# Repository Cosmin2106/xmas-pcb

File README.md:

# ATtiny-powered Christmas Tree

The goal of this project was to create a Christmas decoration that houses a secret puzzle.
The implementation is based around the Microchip ATtiny25V at 1 MHz, which offers 5 GPIO pins with pin change interrupts.
The board is driven by a single CR2032 battery and features a button for user input.

The MCU can be either programmed using the exposed connectors of the "tree trunk", or with an SOIC-8 clip.
In my case, I opted for the latter.
Details regarding the programmer can be found in [this repository](https://github.com/Cosmin2106/arduinoisp-attiny-8-pin-pcb).

## Modes of Operation

When we turn on the board, we can perform a quick check to see if the button is already being held down or not.
If we encounter a normal power cycle, we enter **christmas decoration mode**.
The button is now dedicated to cycling through different prebuilt light shows.
If the button is being pressed at boot, we enter **game mode** instead.
The game idea is inspired by [Pop The Lock](https://apps.apple.com/us/app/pop-the-lock/id979100082) and [Stop Me](https://github.com/SolderedElectronics/-Stop-me-game-solder-kit).
To optimize flash usage, we *emulate randomness* by using a linear congruential generator as PRNG.
At the end of each game, the board displays the total number of points using the "branch" LEDs: one left blink means +10, one right blink, +1.
Using EEPROM flags, we can remember if the user surpassed a hard-coded points threshold in order to unlock secret light shows in the other mode.

## BOM

Designator | Footprint | Quantity | Details
---------- | --------- | -------- | -------
BT1 | Renata_HU2032LF | 1 | Renata 701106 holder for CR2032
C1 | 402 | 1 | Ceramic 100 nF
C2 | 402 | 1 | Ceramic 10 uF
D1, D11, D3, D5, D7, D9 | 603 | 6 | Osram LO L29K-J2L1-24-0-2-R18-Z
D10, D12, D2, D4, D6, D8 | 603 | 6 | Osram LY L29K-H1K2-26-0-2-R18-Z
R1, R2, R3, R4 | 402 | 4 | 150 Ω
SW1 | SW_Push_1P1T_NO_CK_KMR2 | 1 | C&K KMR421NGLFS
SW3 | SW_DPDT_CK_JS202011JCQN | 1 | C&K JS202011JCQN
U1 | SOIC-8_5.3x5.3mm_P1.27mm | 1 | ATtiny25V-10SU

## Photos

#### Image Licenses:

- <a href="https://www.flaticon.com/free-icons/ball" title="ball icons">Ball icons created by Good Ware - Flaticon</a>
- <a href="https://www.flaticon.com/free-icons/snowflake" title="snowflake icons">Snowflake icons created by Good Ware - Flaticon</a>
- <a href="https://www.flaticon.com/free-icons/snowflake" title="snowflake icons">Snowflake icons created by kmg design - Flaticon</a>

#### Improvements?

If you have ideas for improvements, please don't hesitate to reach out!
Since this is my first custom PCB project, advice would be highly appreciated! :D

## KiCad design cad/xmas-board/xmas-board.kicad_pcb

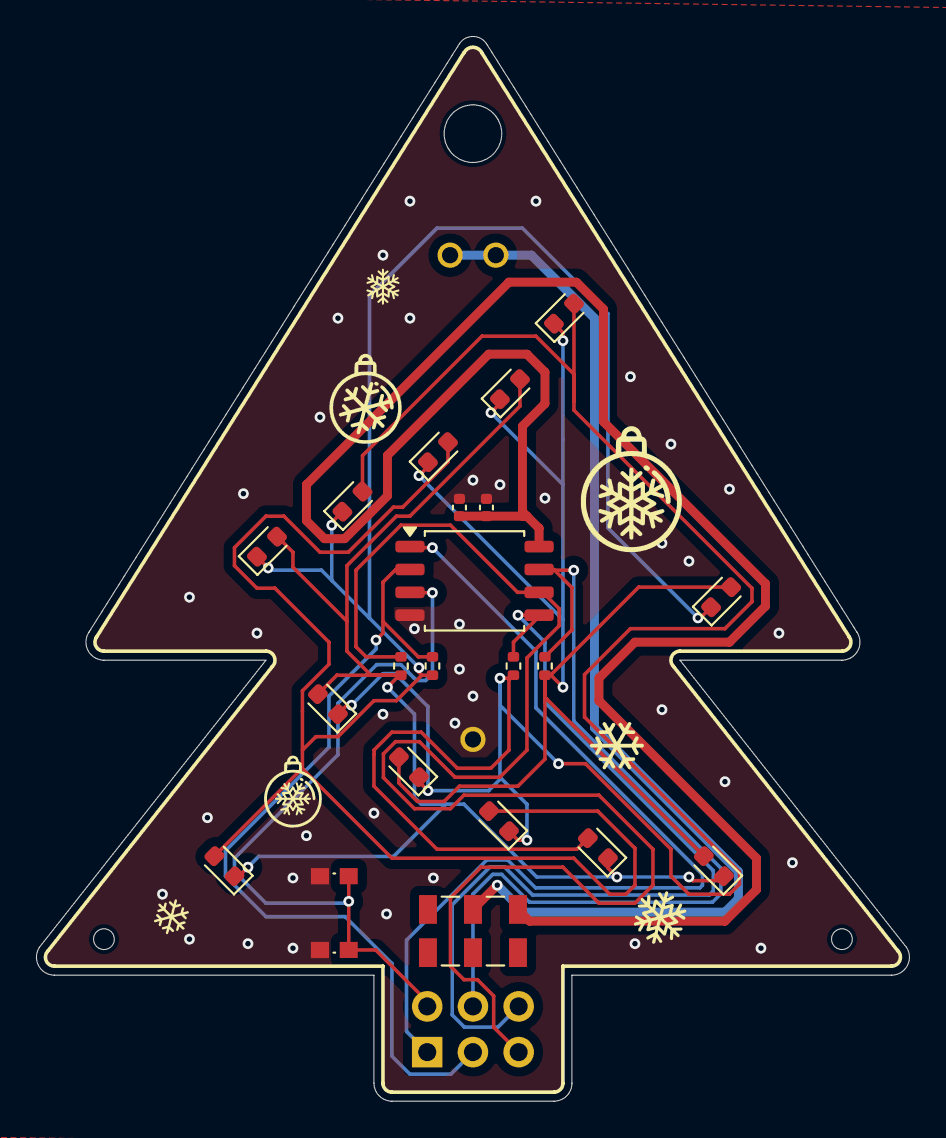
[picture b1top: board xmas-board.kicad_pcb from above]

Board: 2 copper layers, 48.5 x 59.2 mm, 26 parts (1 on the bottom side), 13 nets.

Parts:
BT1: CR2032; Renata_HU2032LF
C1: Ceramic 100nF; C_0402_1005Metric
C2: Ceramic 10uF; C_0402_1005Metric
D1, D3, D5, D7, D9, D11: LO L29K-J2L1-24-0-2-R18-Z; LED_0603_1608Metric
D2, D4, D6, D8, D10, D12: LY L29K-H1K2-26-0-2-R18-Z; LED_0603_1608Metric
H1: Mounting Hole; MountingHole_3.2mm_M3_DIN965
H2, H3: Tooling Hole; ToolingHole_1.152mm
J2: Pin Headers; PinHeader_2x03_P2.54mm_Vertical
R1, R2, R3, R4: 150Ω; R_0402_1005Metric
SW1: KMR421NGLFS; SW_Push_1P1T_NO_CK_KMR2
SW3: On/Off Switch JS202011JCQN; SW_DPDT_CK_JS202011JCQN
U1: ATtiny25V-10S; SOIC-8_5.3x5.3mm_P1.27mm

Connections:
+3.3V: BT1.1 (+), BT1.2 (-), SW3.2 (B)
GND: BT1.3, C1.2, C2.2, SW1.1, U1.4 (GND)
unnamed: D1.2 (A), D4.1 (K), D5.1 (K), D6.1 (K), D8.2 (A), D11.2 (A), R2.2
unnamed: D1.1 (K), D2.1 (K), D3.1 (K), D4.2 (A), D7.2 (A), D10.2 (A), R1.2
unnamed: D3.2 (A), D6.2 (A), D9.2 (A), D10.1 (K), D11.1 (K), D12.1 (K), R4.2
unnamed: D2.2 (A), D5.2 (A), D7.1 (K), D8.1 (K), D9.1 (K), D12.2 (A), R3.2
unnamed: J2.1, U1.1 (~RESET/PB5)
unnamed: J2.2, SW1.2, U1.3 (XTAL2/PB4)
unnamed: J2.3, R4.1, U1.2 (XTAL1/PB3)
unnamed: J2.4, R3.1, U1.7 (PB2)
unnamed: J2.5, R2.1, U1.6 (PB1)
unnamed: J2.6, R1.1, U1.5 (AREF/PB0)
unnamed: C1.1, C2.1, SW3.3 (C), U1.8 (VCC)

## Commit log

2025-11-21 Add mem-optimized fw test for led matrix
2025-11-22 Set light show timer interrupt every 99.3 ms
2025-11-24 Write multiplexing methods to display arbitrary LED patterns
2025-11-25 Optimize mem writes to make LEDs brigther
2025-11-25 Optimize LED clearing and reformat code
2025-11-25 Choose operation modes depending on btn status at boot
2025-11-28 Add PCB design and update firmware to verify LEDs
2025-11-28 Update silkscreen and button position
2025-11-29 Add LED show functionality
2025-11-30 Optimize RAM usage to enable LED shows
2025-12-03 Implement secret operation mode
2025-12-04 Finish game and add unlockable pattern in normal mode
2025-12-04 Add secret message and discover random problem
2025-12-04 Update rand method to use less flash and return all valid LED indices
2025-12-04 Add new light show
2025-12-09 Format code correctly
2025-12-12 Add BOM and image info to README.md
2025-12-12 Add more info to README.md
